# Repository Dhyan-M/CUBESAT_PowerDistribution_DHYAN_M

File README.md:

# CUBESAT_PowerDistribution_DHYAN_M
# CubeSat Electrical Power System (EPS)

A robust, high-reliability Electrical Power System (EPS) designed for a 1U/2U CubeSat architecture. This subsystem handles voltage regulation, dual-rail power distribution, and high-side power switching to ensure stable power delivery to the onboard computer (OBC) and mission payloads under varying battery conditions.

---

## Technical Specifications & Architecture

The EPS manages power distribution by stepping down raw battery voltage into stable DC rails and utilizes logic-level switching for autonomous payload isolation.

### 1. Power Regulation Architecture
* **Primary 5V Rail:** Handled by the **LM7805** linear voltage regulator, providing a dedicated, low-ripple power source for the central microcontroller/OBC (Arduino Nano platform).
* **Secondary 3.3V Rail:** Handled by the **LM1117-3.3** low-dropout (LDO) linear regulator, chained to provide low-noise power for onboard sensors, communication modules, and telemetry systems.

### 2. High-Side Power Switching & Telemetry
* **Power Switching:** Uses **IRF540N N-channel Power MOSFETs** configured for high-efficiency switching paths. This allows the microcontroller to dynamically cut or grant power to specific high-draw payloads to conserve battery.
* **Reverse Current & Spike Protection:** Integrated **1N5822 Schottky barrier diodes** guard the regulation stages against reverse-polarity transients, inductive spikes, and back-EMF from external sub-systems.

---

## System Block Diagram
[ Raw Battery Input ]
│
├──> [ 1N5822 Protection Diode ] ──> [ LM7805 (5V Regulator) ] ──> Stable 5V Rail ──> Arduino Nano (OBC)
│                                                                           │
│                                                                           └──> [ LM1117 (3.3V LDO) ] ──> Stable 3.3V Rail
│
└──> [ IRF540N MOSFET Switches ] ──> Dynamic Payload Isolation Channels (Controlled by OBC GPIO)

---

## Repository Structure

* `/CUBESAT_EPS.kicad_sch` - Main schematic file mapping out electrical connections and circuit design.
* `/CUBESAT_EPS.kicad_pcb` - Physical PCB layout file showing component footprints, track routing, and ground planes.
* `/CUBESAT_EPS.pdf` - High-resolution, production-ready schematic print for quick design reviews.
* `/CUBESAT_EPS.csv` - Bill of Materials (BOM) containing precise component values, quantities, and footprint configurations.
* `/Gerbers/` - Complete fabrication directory containing industry-standard Gerber files (`.gbr`) and Excellon drill files (`.drl`) compiled for PCB manufacturing.

---

## Tools & Technologies Used

* **KiCad EDA (v7/v8):** Used for complete Electronic Design Automation, including schematic capture, custom footprint verification, 2-layer PCB copper routing, zone fills (copper ground planes), and Design Rule Checking (DRC).
* **GitHub:** Utilized for hardware version control, managing design iterations, tracking development branches, and hosting open-source documentation.
* **Markdown:** Used to build clear, accessible engineering documentation for cross-functional team collaboration.

---

## Manufacturing & Assembly Notes

* **Layers:** 2-Layer Board (Top Copper `F.Cu` / Bottom Copper `B.Cu`).
* **Grounding:** Optimized with extensive cross-layer copper pours connected via stitching vias to minimize return path inductance and reduce electromagnetic interference (EMI).
* **Traces:** Power rails are routed with thickened traces to easily sustain maximum current limits without excessive thermal dissipation.

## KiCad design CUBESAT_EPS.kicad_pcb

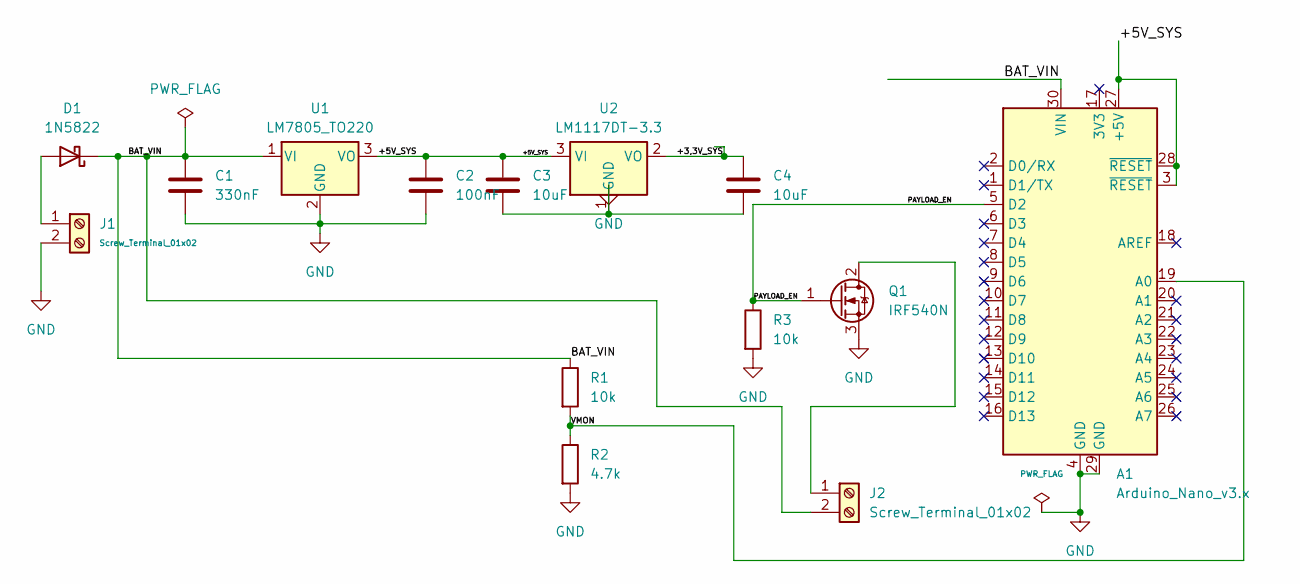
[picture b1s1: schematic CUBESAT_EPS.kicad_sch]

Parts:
A1: Arduino_Nano_v3.x; Arduino_Nano
C1: 330nF; C_Disc_D5.0mm_W2.5mm_P5.00mm
C2: 100nF; C_Disc_D5.0mm_W2.5mm_P5.00mm
C3, C4: 10uF; CP_Radial_D5.0mm_P2.50mm
D1: 1N5822; D_DO-201AD_P15.24mm_Horizontal
J1, J2: Screw_Terminal_01x02; TerminalBlock_Phoenix_MKDS-1,5-2-5.08_1x02_P5.08mm_Horizont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
Q1: IRF540N; TO-220-3_Vertical
R1, R3: 10k; R_Axial_DIN0207_L6.3mm_D2.5mm_P10.16mm_Horizontal
R2: 4.7k; R_Axial_DIN0207_L6.3mm_D2.5mm_P10.16mm_Horizontal
U1: LM7805_TO220; TO-220-3_Vertical
U2: LM1117DT-3.3; TO-220-3_Vertical

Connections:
/+5V_SYS: A1.3 (~RESET), A1.27 (+5V), A1.28 (~RESET), C2.2, C3.1, U1.3 (VO), U2.3 (VI)
/<NO NET>: C4.1, U2.2 (VO)
/BAT_VIN: A1.30 (VIN), C1.2, D1.1 (K), J2.2, R1.1, U1.1 (VI)
/PAYLOAD_EN: A1.5 (D2), Q1.1 (G), R3.1
/VMON: A1.19 (A0), R1.2, R2.1
GND: A1.4 (GND), A1.29 (GND), C1.1, C2.1, C3.2, C4.2, J1.2, Q1.3 (S), R2.2, R3.2, U1.2 (GND), U2.1 (GND)
unnamed: D1.2 (A), J1.1
unnamed: J2.1, Q1.2 (D)

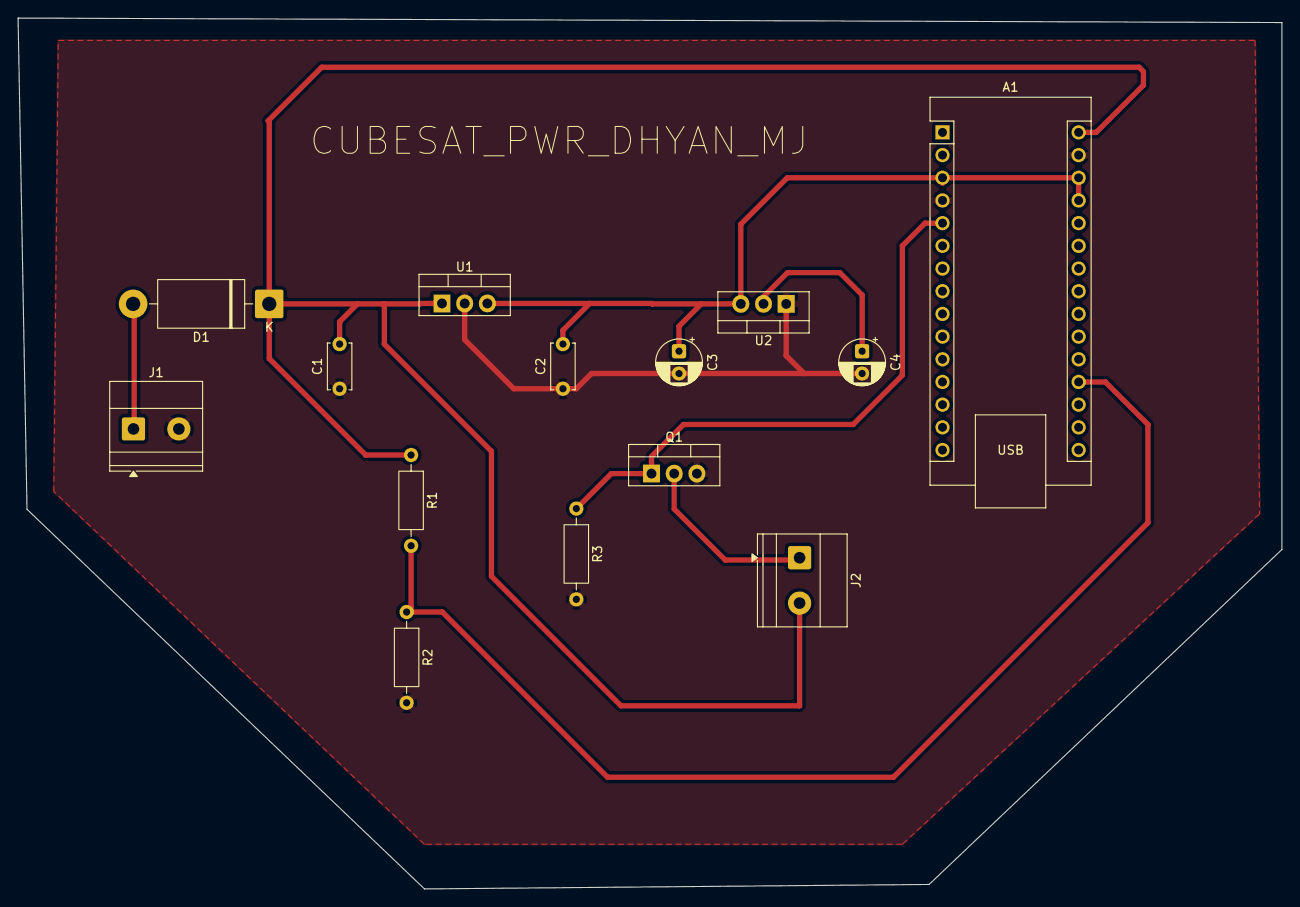
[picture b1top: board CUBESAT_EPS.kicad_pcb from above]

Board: 2 copper layers, 141.5 x 97.5 mm, 14 parts (0 on the bottom side), 8 nets.

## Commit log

2026-05-24 Upload core KiCad project files
2026-05-24 Add fabrication Gerbers and schematic PDF
2026-05-24 Add Bill of Materials (BOM)
2026-05-24 README with EPS details and specifications
    Detailed and accurate information about the CubeSat Electrical Power System, including technical specifications, architecture, system block diagram, repository structure, tools used, and manufacturin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
